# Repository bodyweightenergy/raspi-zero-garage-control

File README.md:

# raspi-zero-garage-control (INCOMPLETE)

Garage Status Indicator/Controller, using a Raspberry Pi Zero W custom Bonnet, with Rust-based software stack.

## Hardware
KiCAD schematics & PCB layout are provided. PCB designed for 10mmx10mm cheap from EasyEDA/JLCPCB. 
Simply generate the GERBERs using KiCAD 5.0 or later, and order from them, and you'll get 20 copies of this Bonnet.

## Software
GPIO & HTTP stack use Rust. While compiling this on the Pi does work, it will take a long time, so setting up a development computer for cross-compiling is recommended.

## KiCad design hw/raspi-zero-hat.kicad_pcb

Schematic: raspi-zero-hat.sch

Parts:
D1, D2: LED; LED_1206_3216Metric_Pad1.42x1.75mm_HandSolder
J1: Screw_Terminal_01x02; TerminalBlock_Phoenix_PT-1,5-2-3.5-H_1x02_P3.50mm_Horizontal
J2: Screw_Terminal_01x03; TerminalBlock_Phoenix_PT-1,5-3-3.5-H_1x03_P3.50mm_Horizontal
K1: G5LE-1; Relay_SPDT_Omron-G5LE-1
MK1, MK2, MK3, MK4: M2.5; MountingHole_2.7mm_M2.5
P1: Conn_02x20_Odd_Even; PinSocket_2x20_P2.54mm_Vertical
Q1: MMBT3904; SOT-23
R1, R2: R; R_1206_3216Metric_Pad1.42x1.75mm_HandSolder

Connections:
+3V3: P1.1, P1.17
+5V: J1.1, P1.2, P1.4, Q1.3 (C)
/GPIO2(SDA1): P1.3
/GPIO3(SCL1): P1.5
/GPIO4(GCLK): P1.7
/GPIO5: P1.29
/GPIO6: P1.31
/GPIO7(SPI1_CE_N): P1.26
/GPIO8(SPI0_CE_N): P1.24
/GPIO9(SPI0_MISO): P1.21
/GPIO10(SPI0_MOSI): P1.19
/GPIO11(SPI0_SCK): P1.23
/GPIO12(PWM0): P1.32
/GPIO13(PWM1): P1.33
/GPIO15(RXD0): P1.10, Q1.1 (B)
/GPIO16: P1.36
/GPIO17(GEN0): P1.11
/GPIO18(GEN1)(PWM0): P1.12
/GPIO19(SPI1_MISO): P1.35
/GPIO20(SPI1_MOSI): P1.38
/GPIO21(SPI1_SCK): P1.40
/GPIO22(GEN3): P1.15
/GPIO23(GEN4): J1.2, P1.16
/GPIO24(GEN5): D1.2, P1.18
/GPIO25(GEN6): P1.22
/GPIO26: P1.37
/GPIO27(GEN2): P1.13
/ID_SC: P1.28
/ID_SD: P1.27
GND: K1.2, P1.6, P1.9, P1.14, P1.20, P1.25, P1.30, P1.34, P1.39, R1.2, R2.2
unnamed: D1.1, R1.1
unnamed: D2.1, R2.1
unnamed: D2.2, K1.5, Q1.2 (E)
unnamed: J2.1, K1.4
unnamed: J2.2, K1.1
unnamed: J2.3, K1.3

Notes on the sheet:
ID_SD and ID_SC PINS: These pins are reserved for HAT ID EEPROM. At boot time this I2C interface will be interrogated to look for an EEPROM that identifes the attached board and allows automagic setup of the GPIOs (and optionally, Linux drivers). DO NOT USE these pins for anything other than attach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
Mounting Holes

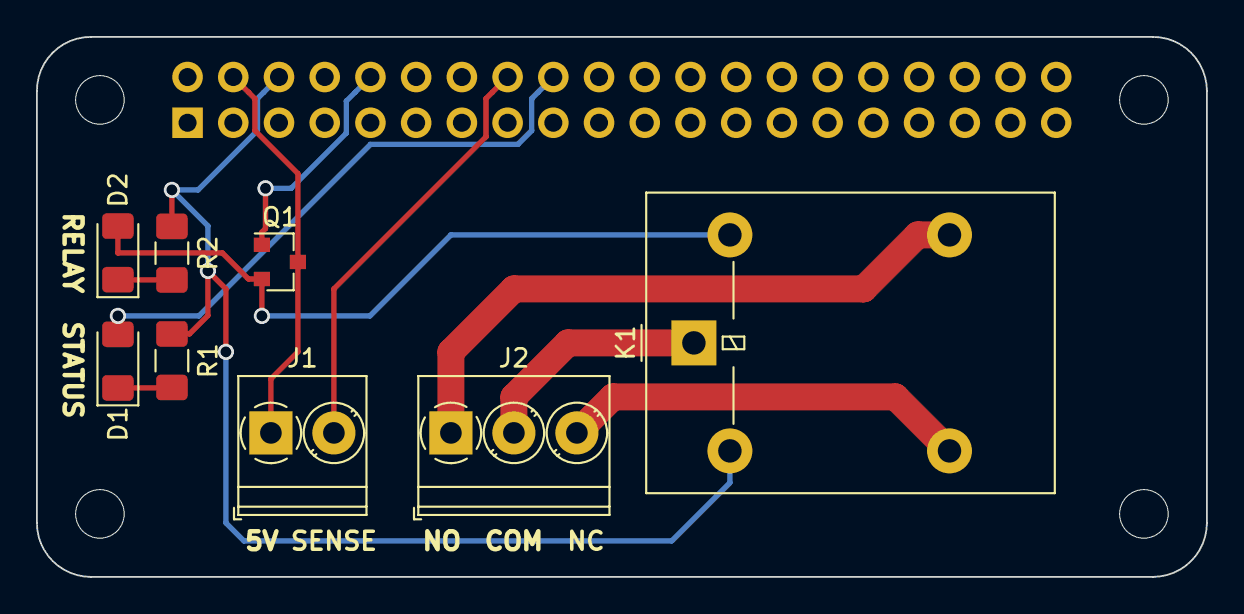
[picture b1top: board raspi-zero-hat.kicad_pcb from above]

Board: 2 copper layers, 65.0 x 30.0 mm, 13 parts (1 on the bottom side), 12 nets.

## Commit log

2018-08-15 initial commit (standard size, no relay driver MOSFET)
2018-08-16 added NPN for relay drive. duplicated PCB w/ perforations.
2018-11-27 moved to hardware folder
2018-11-27 initial commit of Rust source code + build script
2018-12-13 moved relay control pin to pin 10 (pin 8 was pulled up on boot, causing an unintended relay toggle).
2018-12-28 switched to actix-web, added toggle and sense methods
2018-12-29 added status LED heartbeat
